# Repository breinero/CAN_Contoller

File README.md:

# Programable CAN Controller Node

This design is a generic Controller Area Network (CAN) controller which can be programmed, and reprogramed for use in a given CAN compliant network. It is designed so that a user can create, or order many, duplicates of this board in batches, and then program each individual board with a specific function within a network. This board has also been designed to be as physically small as possible, so that this same board design can be used through out a given network. This project is purely a hardware design, and does not include an software or firmware to for communicating on a CAN network. 

This board is intended to be used in a variety of embedded use cases, but I inted to use this board for retrofitting a CAN network into vintage automobiles and in homebuilt and experimental aircraft. For that reaon the specific components of the design were selected for their quality and reliability.

## Features
1. Compliant with CAN Bus standards
1. The controller node is extensible, where the same unit can be configured and reconfigured to perform different functions
    1. Nodes of this design can collect sensor data, such as oil pressure, fuel level, or vehicle speed, and be able to control components such as turn signals and headlights.
1. Control at least 3 relays independently. E.G. headlights, high beams, turn signal. Or, control one servo 
1. Reprogrammable. The controller code can be updated with bug fixes and improvements
1. Can be added to an existing network with need to reprogram nodes on that network

## Non-Functional Requirements
1. Can be economically ordered via a PCB service
    1. Easy for myself, hobbyests, enthusiasts, or anyone else to acquire in batch sizes between 10 to 100 units
1. Minimal size, so that it can be used in tight spaces or within small component assemblies
1. Robust and reliable enough for automotive and experimental aircraft applications. 

## Non-Goals
1. Easily of assembly. Achieving the smallest footprint and volume takes priority over being able to hand solder this design. Folks have the option to over this part from a PCB assembly service or vendor, if they have difficulty assembling the board. 

# License 
The design files and documentation in this project are licensed under the [Creative Commons Attribution-ShareAlike 4.0 International license (CC BY-SA 4.0)](LICENSE)

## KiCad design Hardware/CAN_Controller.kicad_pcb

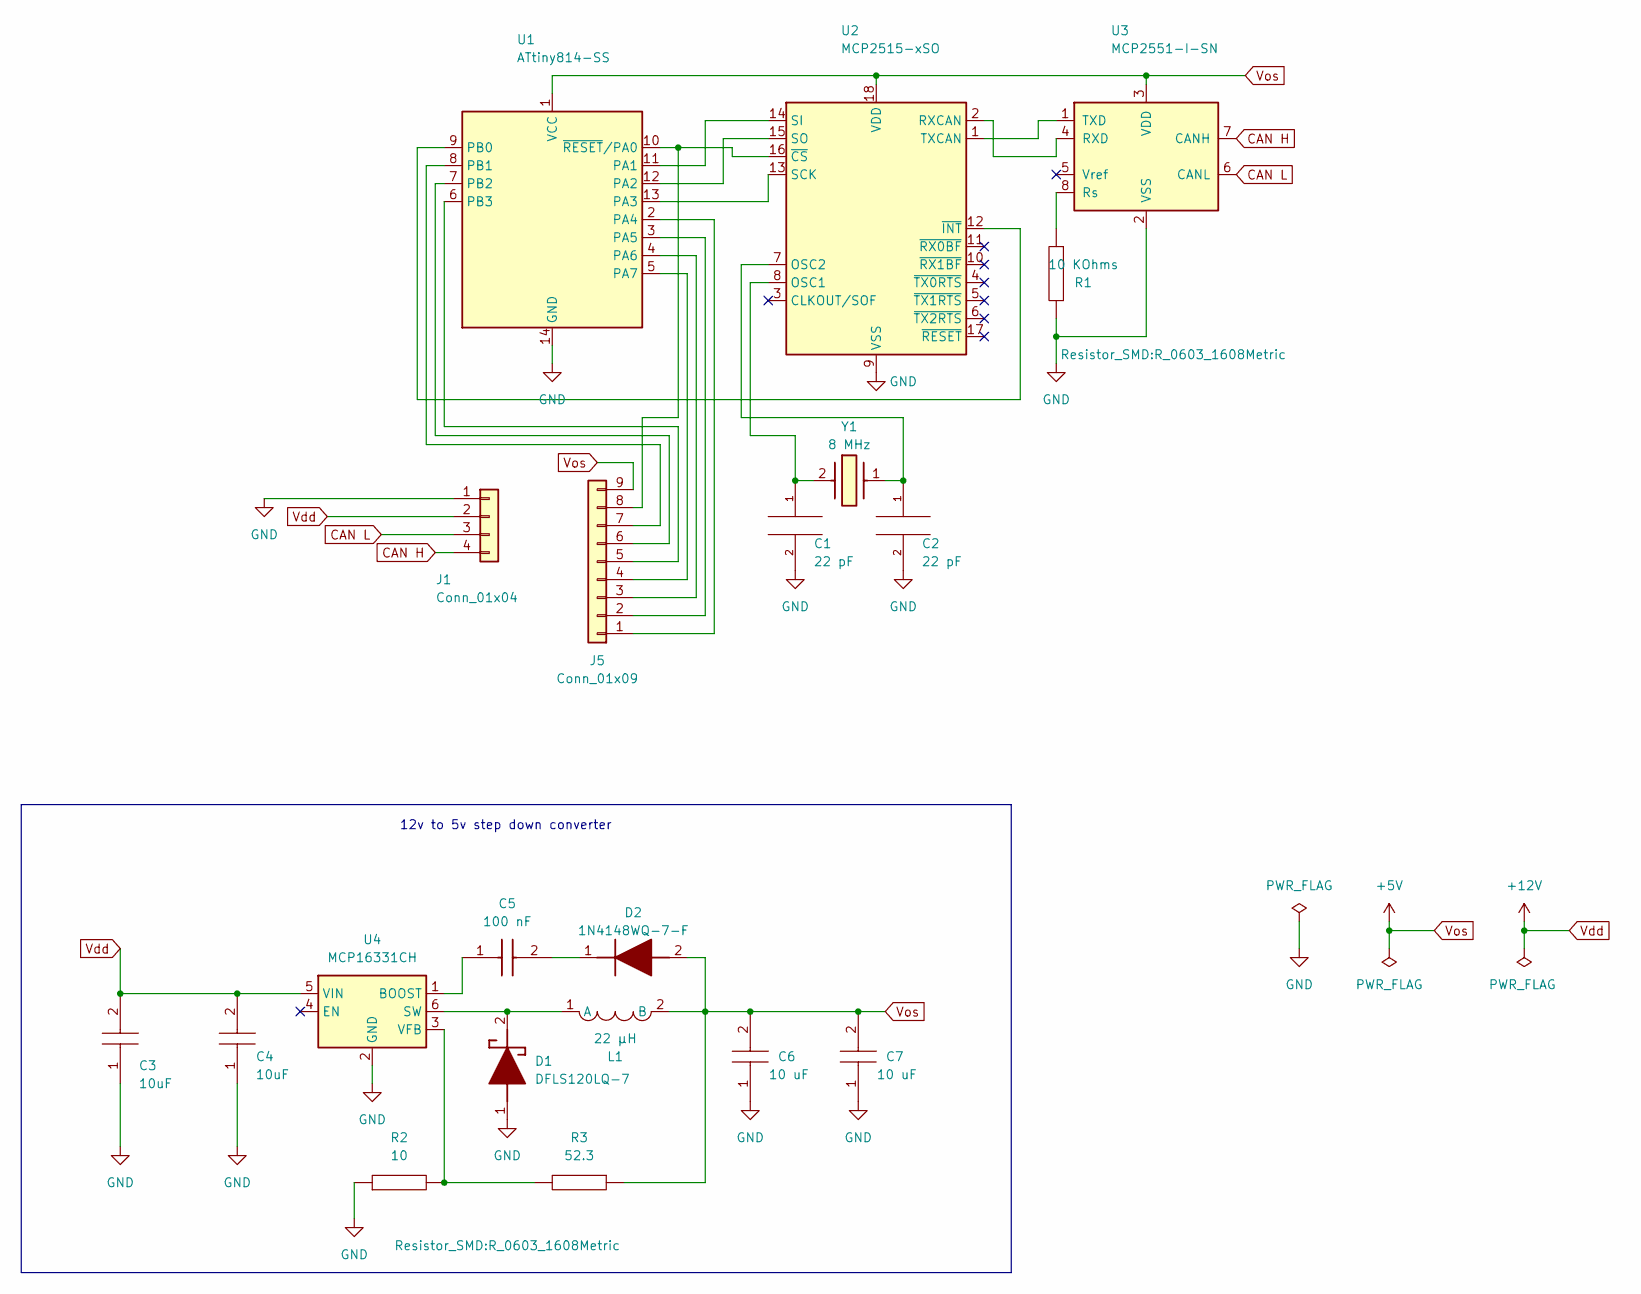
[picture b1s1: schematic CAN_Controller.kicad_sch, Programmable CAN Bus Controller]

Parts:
C1, C2: 22 pF; C_0603_1608Metric; Manufacturer_Part_Number C0603C220K3RACAUTO
C3, C4: 10uF; C3225_Commercial; Mouser Part Number 810-C3225X7R1H106MAC
C5: 100 nF; CAPC1608X90N; Mouser Part Number 581-060316C104K
C6, C7: 10 uF; CAPC3216X180N; Mouser Part Number 810-C3216X7R1E106K
D1: DFLS120LQ-7; DFLS120LQ7; Mouser Part Number 621-DFLS120LQ7
D2: 1N4148WQ-7-F; SOD3716X145N; Mouser Part Number 621-1N4148WQ-7-F
J1: Conn_01x04; PinHeader_1x04_P2.54mm_Vertical
J5: Conn_01x09; PinHeader_1x09_P2.54mm_Vertical
L1: 22 µH; Inductor_MSS1048-223
R1: 10 KOhms; R_0603_1608Metric
R2: 10; R_0603_1608Metric
R3: 52.3; R_0603_1608Metric
U1: ATtiny814-SS; SOIC-14_3.9x8.7mm_P1.27mm
U2: MCP2515-xSO; SOIC-18W_7.5x11.6mm_P1.27mm
U3: MCP2551-I-SN; SOIC-8_3.9x4.9mm_P1.27mm
U4: MCP16331CH; SOT-23-6
Y1: 8 MHz; ECS80830QVSTR; Mouser Part Number 520-80-8-30Q-VST

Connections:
CAN H: J1.4, U3.7 (CANH)
CAN L: J1.3, U3.6 (CANL)
GND: C1.2, C2.2, C3.1, C4.1, C6.1, C7.1, D1.1 (A), J1.1, R1.1, R2.1, U1.14 (GND), U2.9 (VSS), U3.2 (VSS), U4.2 (GND)
unnamed: D1.2 (K), L1.1 (A), U4.6 (SW)
unnamed: C5.2, D2.1 (K)
unnamed: J5.1, U1.2 (PA4)
unnamed: J5.2, U1.3 (PA5)
unnamed: J5.3, U1.4 (PA6)
unnamed: J5.4, U1.5 (PA7)
unnamed: J5.5, U1.6 (PB3)
unnamed: J5.6, U1.7 (PB2)
unnamed: J5.7, U1.8 (PB1)
unnamed: J5.8, U1.10 (~RESET/PA0), U2.16 (~CS)
unnamed: U1.11 (PA1), U2.14 (SI)
unnamed: U1.12 (PA2), U2.15 (SO)
unnamed: U1.13 (PA3), U2.13 (SCK)
unnamed: U1.9 (PB0), U2.12 (~INT)
unnamed: C1.1, U2.8 (OSC1), Y1.2 (OUT/IN)
unnamed: C2.1, U2.7 (OSC2), Y1.1 (IN/OUT)
unnamed: U2.2 (RXCAN), U3.4 (RXD)
unnamed: U2.1 (TXCAN), U3.1 (TXD)
unnamed: R1.2, U3.8 (Rs)
unnamed: C5.1, U4.1 (BOOST)
unnamed: R2.2, R3.2, U4.3 (VFB)
Vdd: C3.2, C4.2, J1.2, U4.5 (VIN)
Vos: C6.2, C7.2, D2.2 (A), J5.9, L1.2 (B), R3.1, U1.1 (VCC), U2.18 (VDD), U3.3 (VDD)

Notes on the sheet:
12v to 5v step down converter

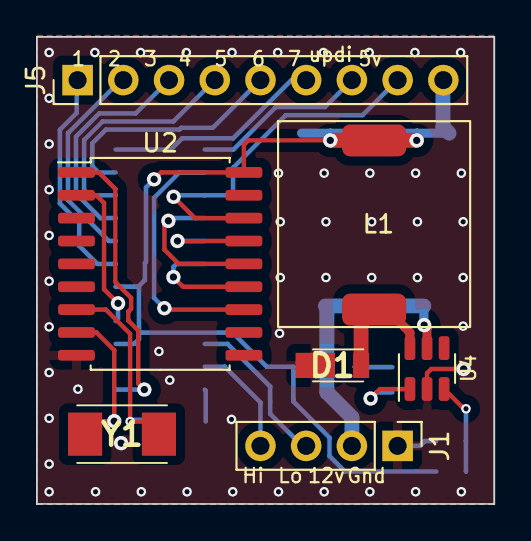
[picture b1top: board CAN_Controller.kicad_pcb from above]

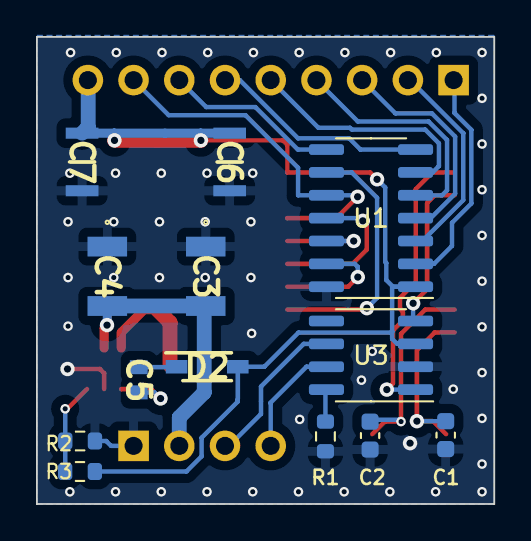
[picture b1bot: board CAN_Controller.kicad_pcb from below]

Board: 2 copper layers, 25.4 x 26.0 mm, 20 parts (13 on the bottom side), 26 nets.

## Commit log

2023-02-14 Added License, and double checked polarity of SMDs
2023-02-14 added picture and link to license from README
2023-03-19 rearrainged components to reduce board size and added project footprints
2023-03-19 removed gerber and drill file achive
2023-04-23 Reduced PCB footprint
